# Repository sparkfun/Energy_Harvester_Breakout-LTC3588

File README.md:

SparkFun Energy Harvester Breakout - LTC3588
========================================

[*SparkFun Energy Harvester Breakout - LTC3588 (BOB-09946)*](https://www.sparkfun.com/products/9946)

This breakout board uses the LTC3588 Piezoelectric Energy Harvester from Linear Technologies. 
This board can be used not only for harvesting piezoelectric energy, but solar energy as well. 
There is a bridge rectified input for piezo elements (PZ1 and PZ2) and a direct input (VIN) for DC sources. 
Both are clamped to 20V. 
In addition, the board can simply be used as a standalone nanopower buck regulator.

Repository Contents
-------------------

* **/Hardware** - Eagle design files (.brd, .sch)
* **/Production** - Production panel files (.brd)

Documentation
--------------
* **[SparkFun Fritzing repo](https://github.com/sparkfun/Fritzing_Parts)** - Fritzing diagrams for SparkFun products.
* **[SparkFun 3D Model repo](https://github.com/sparkfun/3D_Models)** - 3D models of SparkFun products. 

License Information
-------------------
This product is _**open source**_! 

The **hardware** is released under [Creative Commons ShareAlike 4.0 International](https://creativecommons.org/licenses/by-sa/4.0/).

Please use, reuse, and modify these files as you see fit. Please maintain attribution to SparkFun Electronics and release anything derivative under the same license.

Distributed as-is; no warranty is given.

- Your friends at SparkFun.

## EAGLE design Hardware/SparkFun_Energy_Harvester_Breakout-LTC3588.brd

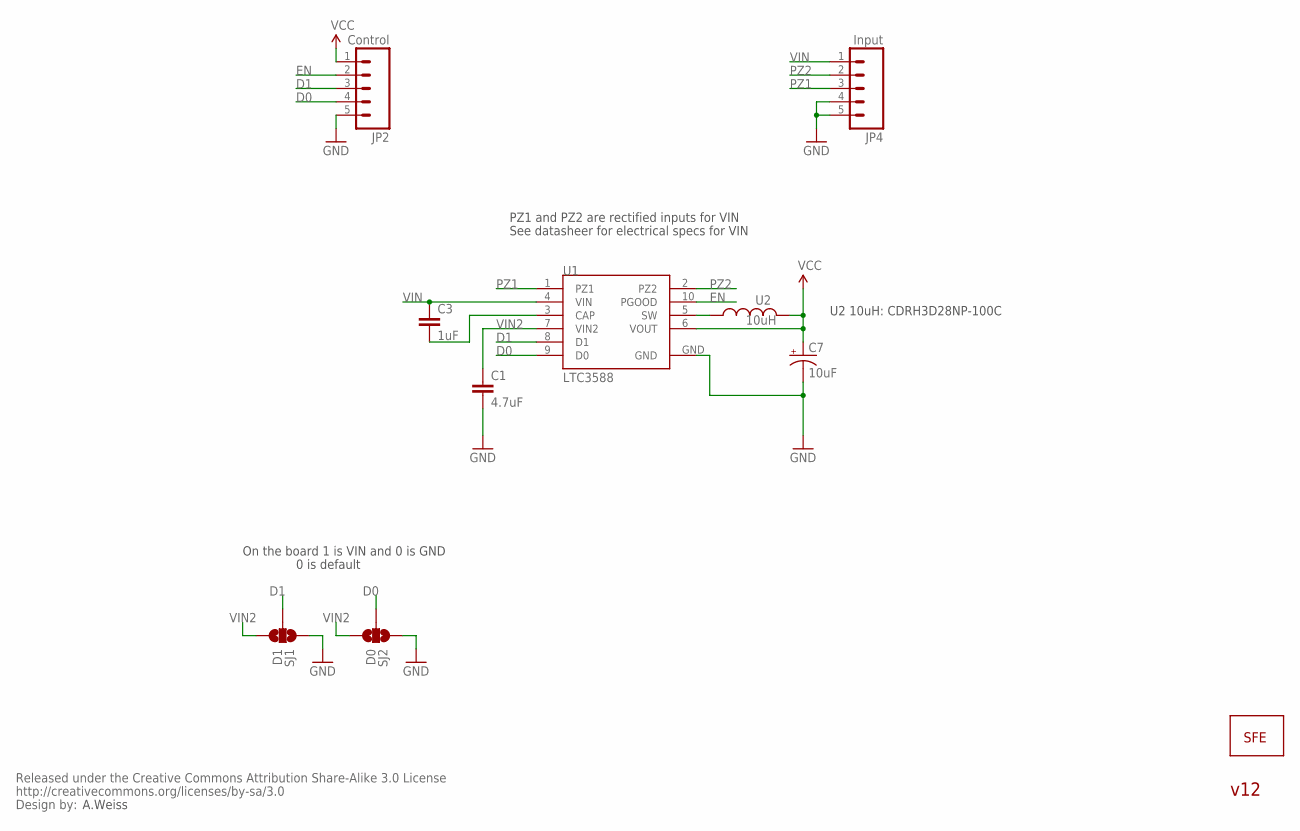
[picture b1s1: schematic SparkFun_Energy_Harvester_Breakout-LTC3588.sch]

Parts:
C1: 4.7uF; 0402-CAP
C3: 1uF; 0402-CAP
C7: 10uF; EIA3216
JP1: LOGO-SFESK; SFE-LOGO-FLAME
JP2: Control; 1X05
JP4: Input; 1X05
SJ1: D1; SJ_3_PASTE2&3
SJ2: D0; SJ_3_PASTE1&2
U1: LTC3588; MSOP-10-GNDPAD
U2: 10uH; CDRH3D28
U$1: CREATIVE_COMMONS

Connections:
D0: JP2.4, SJ2.2, U1.9 (D0)
D1: JP2.3, SJ1.2, U1.8 (D1)
EN: JP2.2, U1.10 (PGOOD)
GND: C1.2, C7.C (-), JP2.5, JP4.4, JP4.5, SJ1.1, SJ2.1, U1.GND
unnamed: C3.2, U1.3 (CAP)
unnamed: U1.5 (SW), U2.1
PZ1: JP4.3, U1.1 (PZ1)
PZ2: JP4.2, U1.2 (PZ2)
VCC: C7.A (+), JP2.1, U1.6 (VOUT), U2.2
VIN: C3.1, JP4.1, U1.4 (VIN)
VIN2: C1.1, SJ1.3, SJ2.3, U1.7 (VIN2)

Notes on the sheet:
U2 10uH: CDRH3D28NP-100C
A.Weiss
On the board 1 is VIN and 0 is GND
0 is default
PZ1 and PZ2 are rectified inputs for VIN
See datasheer for electrical specs for VIN
v12

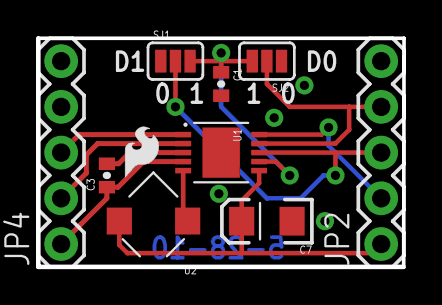
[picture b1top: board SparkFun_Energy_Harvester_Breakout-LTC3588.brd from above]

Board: 2 copper layers, 20.3 x 12.7 mm, 11 parts (0 on the bottom side), 11 nets.

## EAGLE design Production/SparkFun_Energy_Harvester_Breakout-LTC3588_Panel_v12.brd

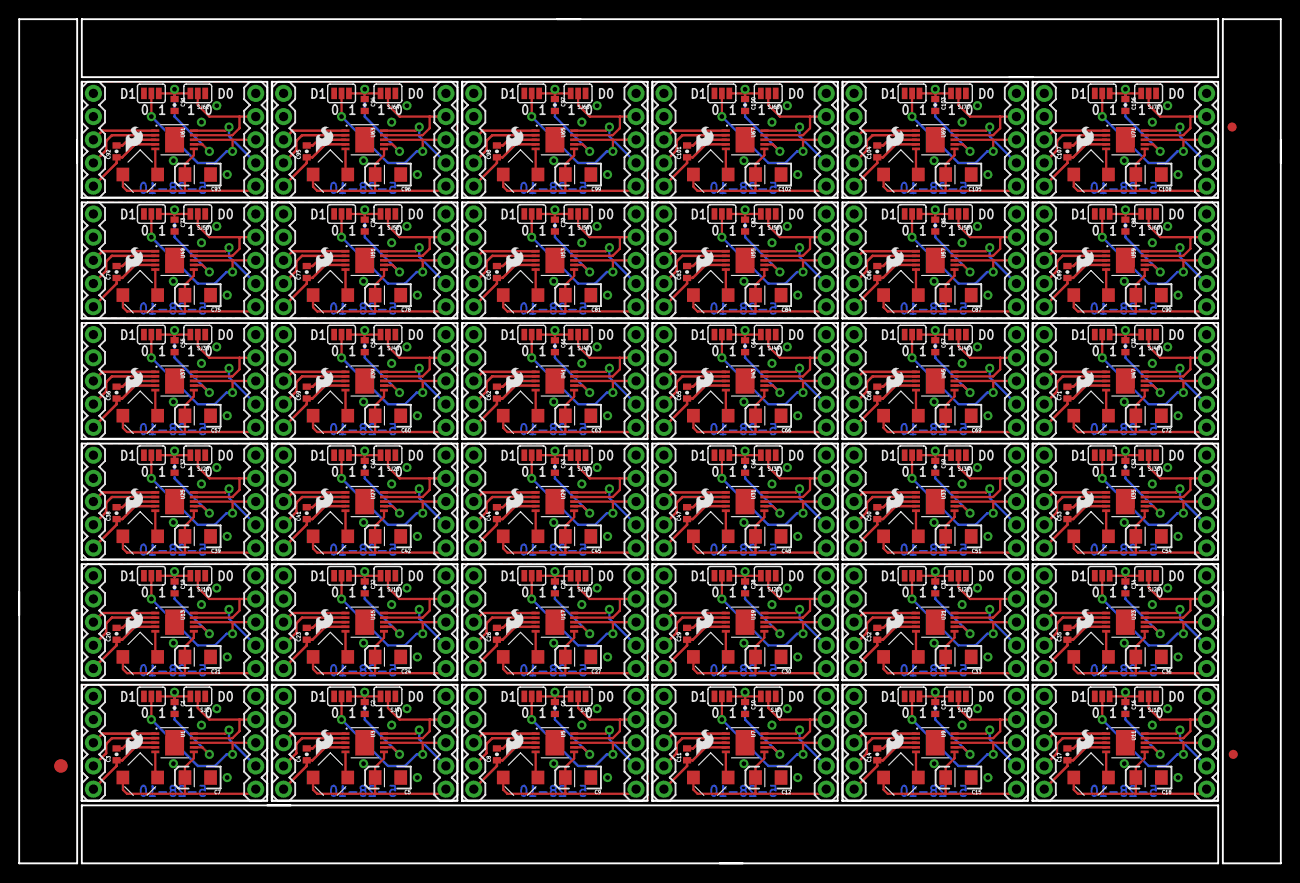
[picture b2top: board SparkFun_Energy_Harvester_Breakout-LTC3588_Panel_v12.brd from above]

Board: 2 copper layers, 138.1 x 92.4 mm, 363 parts (0 on the bottom side), 396 nets.

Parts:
C1, C2, C6, C10, C13, C16, C19, C22, C25, C28, C31, C34, C37, C40, C43, C46, C49, C52, C55, C58, C61, C64, C67, C70, C73, C76, C79, C82, C85, C88, C91, C94, C97, C100, C103, C106: 4.7uF; 0402-CAP
C3, C4, C8, C11, C14, C17, C20, C23, C26, C29, C32, C35, C38, C41, C44, C47, C50, C53, C56, C59, C62, C65, C68, C71, C74, C77, C80, C83, C86, C89, C92, C95, C98, C101, C104, C107: 1uF; 0402-CAP
C5, C7, C9, C12, C15, C18, C21, C24, C27, C30, C33, C36, C39, C42, C45, C48, C51, C54, C57, C60, C63, C66, C69, C72, C75, C78, C81, C84, C87, C90, C93, C96, C99, C102, C105, C108: 10uF; EIA3216
E$1: FIDUCIAL-1.5X3
E$5, E$7: FIDUCIAL-1X2
JP1, JP6, JP9, JP12, JP15, JP18, JP21, JP24, JP27, JP30, JP33, JP36, JP39, JP42, JP45, JP48, JP51, JP54, JP57, JP60, JP63, JP66, JP69, JP72, JP75, JP78, JP81, JP84, JP87, JP90, JP93, JP96, JP99, JP102, JP105, JP108: LOGO-SFESK; SFE-LOGO-FLAME
JP2, JP3, JP7, JP10, JP13, JP16, JP19, JP22, JP25, JP28, JP31, JP34, JP37, JP40, JP43, JP46, JP49, JP52, JP55, JP58, JP61, JP64, JP67, JP70, JP73, JP76, JP79, JP82, JP85, JP88, JP91, JP94, JP97, JP100, JP103, JP106: Control; 1X05
JP4, JP5, JP8, JP11, JP14, JP17, JP20, JP23, JP26, JP29, JP32, JP35, JP38, JP41, JP44, JP47, JP50, JP53, JP56, JP59, JP62, JP65, JP68, JP71, JP74, JP77, JP80, JP83, JP86, JP89, JP92, JP95, JP98, JP101, JP104, JP107: Input; 1X05
SJ1, SJ3, SJ5, SJ7, SJ9, SJ11, SJ13, SJ15, SJ17, SJ19, SJ21, SJ23, SJ25, SJ27, SJ29, SJ31, SJ33, SJ35, SJ37, SJ39, SJ41, SJ43, SJ45, SJ47, SJ49, SJ51, SJ53, SJ55, SJ57, SJ59, SJ61, SJ63, SJ65, SJ67, SJ69, SJ71: D1; SJ_3_PASTE2&3
SJ2, SJ4, SJ6, SJ8, SJ10, SJ12, SJ14, SJ16, SJ18, SJ20, SJ22, SJ24, SJ26, SJ28, SJ30, SJ32, SJ34, SJ36, SJ38, SJ40, SJ42, SJ44, SJ46, SJ48, SJ50, SJ52, SJ54, SJ56, SJ58, SJ60, SJ62, SJ64, SJ66, SJ68, SJ70, SJ72: D0; SJ_3_PASTE1&2
U1, U3, U5, U7, U9, U11, U13, U15, U17, U19, U21, U23, U25, U27, U29, U31, U33, U35, U37, U39, U41, U43, U45, U47, U49, U51, U53, U55, U57, U59, U61, U63, U65, U67, U69, U71: LTC3588; MSOP-10-GNDPAD
U2, U4, U6, U8, U10, U12, U14, U16, U18, U20, U22, U24, U26, U28, U30, U32, U34, U36, U38, U40, U42, U44, U46, U48, U50, U52, U54, U56, U58, U60, U62, U64, U66, U68, U70, U72: 10uH; CDRH3D28

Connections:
D0: JP2.4, SJ2.2, U1.9
D1: JP2.3, SJ1.2, U1.8
D2: JP3.3, SJ3.2, U3.8
D3: JP3.4, SJ4.2, U3.9
D4: JP7.3, SJ5.2, U5.8
D5: JP7.4, SJ6.2, U5.9
D6: JP10.3, SJ7.2, U7.8
D7: JP10.4, SJ8.2, U7.9
D8: JP13.3, SJ9.2, U9.8
D9: JP13.4, SJ10.2, U9.9
D10: JP16.3, SJ11.2, U11.8
D11: JP16.4, SJ12.2, U11.9
D12: JP19.3, SJ13.2, U13.8
D13: JP19.4, SJ14.2, U13.9
D14: JP22.3, SJ15.2, U15.8
D15: JP22.4, SJ16.2, U15.9
D16: JP25.3, SJ17.2, U17.8
D17: JP25.4, SJ18.2, U17.9
D18: JP28.3, SJ19.2, U19.8
D19: JP28.4, SJ20.2, U19.9
D20: JP31.3, SJ21.2, U21.8
D21: JP31.4, SJ22.2, U21.9
D22: JP34.3, SJ23.2, U23.8
D23: JP34.4, SJ24.2, U23.9
D24: JP37.3, SJ25.2, U25.8
D25: JP37.4, SJ26.2, U25.9
D26: JP40.3, SJ27.2, U27.8
D27: JP40.4, SJ28.2, U27.9
D28: JP43.3, SJ29.2, U29.8
D29: JP43.4, SJ30.2, U29.9
D30: JP46.3, SJ31.2, U31.8
D31: JP46.4, SJ32.2, U31.9
D32: JP49.3, SJ33.2, U33.8
D33: JP49.4, SJ34.2, U33.9
D34: JP52.3, SJ35.2, U35.8
D35: JP52.4, SJ36.2, U35.9
D36: JP55.3, SJ37.2, U37.8
D37: JP55.4, SJ38.2, U37.9
D38: JP58.3, SJ39.2, U39.8
D39: JP58.4, SJ40.2, U39.9
D40: JP61.3, SJ41.2, U41.8
D41: JP61.4, SJ42.2, U41.9
D42: JP64.3, SJ43.2, U43.8
D43: JP64.4, SJ44.2, U43.9
D44: JP67.3, SJ45.2, U45.8
D45: JP67.4, SJ46.2, U45.9
D46: JP70.3, SJ47.2, U47.8
D47: JP70.4, SJ48.2, U47.9
D48: JP73.3, SJ49.2, U49.8
D49: JP73.4, SJ50.2, U49.9
D50: JP76.3, SJ51.2, U51.8
D51: JP76.4, SJ52.2, U51.9
D52: JP79.3, SJ53.2, U53.8
D53: JP79.4, SJ54.2, U53.9
D54: JP82.3, SJ55.2, U55.8
D55: JP82.4, SJ56.2, U55.9
D56: JP85.3, SJ57.2, U57.8
D57: JP85.4, SJ58.2, U57.9
D58: JP88.3, SJ59.2, U59.8
D59: JP88.4, SJ60.2, U59.9
D60: JP91.3, SJ61.2, U61.8
D61: JP91.4, SJ62.2, U61.9
D62: JP94.3, SJ63.2, U63.8
D63: JP94.4, SJ64.2, U63.9
D64: JP97.3, SJ65.2, U65.8
D65: JP97.4, SJ66.2, U65.9
D66: JP100.3, SJ67.2, U67.8
D67: JP100.4, SJ68.2, U67.9
D68: JP103.3, SJ69.2, U69.8
D69: JP103.4, SJ70.2, U69.9
D70: JP106.3, SJ71.2, U71.8
D71: JP106.4, SJ72.2, U71.9
EN: JP2.2, U1.10
EN1: JP3.2, U3.10
EN2: JP7.2, U5.10
EN3: JP10.2, U7.10
EN4: JP13.2, U9.10
EN5: JP16.2, U11.10
EN6: JP19.2, U13.10
EN7: JP22.2, U15.10
EN8: JP25.2, U17.10
EN9: JP28.2, U19.10
EN10: JP31.2, U21.10
EN11: JP34.2, U23.10
EN12: JP37.2, U25.10
EN13: JP40.2, U27.10
EN14: JP43.2, U29.10
EN15: JP46.2, U31.10
EN16: JP49.2, U33.10
EN17: JP52.2, U35.10
EN18: JP55.2, U37.10
EN19: JP58.2, U39.10
EN20: JP61.2, U41.10
EN21: JP64.2, U43.10
EN22: JP67.2, U45.10
EN23: JP70.2, U47.10
EN24: JP73.2, U49.10
EN25: JP76.2, U51.10
EN26: JP79.2, U53.10
EN27: JP82.2, U55.10
EN28: JP85.2, U57.10
EN29: JP88.2, U59.10
EN30: JP91.2, U61.10
EN31: JP94.2, U63.10
EN32: JP97.2, U65.10
EN33: JP100.2, U67.10
EN34: JP103.2, U69.10
EN35: JP106.2, U71.10
GND: C1.2, C7.C, JP2.5, JP4.4, JP4.5, SJ1.1, SJ2.1, U1.GND
GND1: C2.2, C5.C, JP3.5, JP5.4, JP5.5, SJ3.1, SJ4.1, U3.GND
GND2: C6.2, C9.C, JP7.5, JP8.4, JP8.5, SJ5.1, SJ6.1, U5.GND
GND3: C10.2, C12.C, JP10.5, JP11.4, JP11.5, SJ7.1, SJ8.1, U7.GND
GND4: C13.2, C15.C, JP13.5, JP14.4, JP14.5, SJ9.1, SJ10.1, U9.GND
GND5: C16.2, C18.C, JP16.5, JP17.4, JP17.5, SJ11.1, SJ12.1, U11.GND
GND6: C19.2, C21.C, JP19.5, JP20.4, JP20.5, SJ13.1, SJ14.1, U13.GND
GND7: C22.2, C24.C, JP22.5, JP23.4, JP23.5, SJ15.1, SJ16.1, U15.GND
GND8: C25.2, C27.C, JP25.5, JP26.4, JP26.5, SJ17.1, SJ18.1, U17.GND
GND9: C28.2, C30.C, JP28.5, JP29.4, JP29.5, SJ19.1, SJ20.1, U19.GND
GND10: C31.2, C33.C, JP31.5, JP32.4, JP32.5, SJ21.1, SJ22.1, U21.GND
GND11: C34.2, C36.C, JP34.5, JP35.4, JP35.5, SJ23.1, SJ24.1, U23.GND
GND12: C37.2, C39.C, JP37.5, JP38.4, JP38.5, SJ25.1, SJ26.1, U25.GND
GND13: C40.2, C42.C, JP40.5, JP41.4, JP41.5, SJ27.1, SJ28.1, U27.GND
GND14: C43.2, C45.C, JP43.5, JP44.4, JP44.5, SJ29.1, SJ30.1, U29.GND
GND15: C46.2, C48.C, JP46.5, JP47.4, JP47.5, SJ31.1, SJ32.1, U31.GND
GND16: C49.2, C51.C, JP49.5, JP50.4, JP50.5, SJ33.1, SJ34.1, U33.GND
GND17: C52.2, C54.C, JP52.5, JP53.4, JP53.5, SJ35.1, SJ36.1, U35.GND
GND18: C55.2, C57.C, JP55.5, JP56.4, JP56.5, SJ37.1, SJ38.1, U37.GND
GND19: C58.2, C60.C, JP58.5, JP59.4, JP59.5, SJ39.1, SJ40.1, U39.GND
GND20: C61.2, C63.C, JP61.5, JP62.4, JP62.5, SJ41.1, SJ42.1, U41.GND
GND21: C64.2, C66.C, JP64.5, JP65.4, JP65.5, SJ43.1, SJ44.1, U43.GND
GND22: C67.2, C69.C, JP67.5, JP68.4, JP68.5, SJ45.1, SJ46.1, U45.GND
GND23: C70.2, C72.C, JP70.5, JP71.4, JP71.5, SJ47.1, SJ48.1, U47.GND
GND24: C73.2, C75.C, JP73.5, JP74.4, JP74.5, SJ49.1, SJ50.1, U49.GND
GND25: C76.2, C78.C, JP76.5, JP77.4, JP77.5, SJ51.1, SJ52.1, U51.GND
GND26: C79.2, C81.C, JP79.5, JP80.4, JP80.5, SJ53.1, SJ54.1, U53.GND
GND27: C82.2, C84.C, JP82.5, JP83.4, JP83.5, SJ55.1, SJ56.1, U55.GND
GND28: C85.2, C87.C, JP85.5, JP86.4, JP86.5, SJ57.1, SJ58.1, U57.GND
GND29: C88.2, C90.C, JP88.5, JP89.4, JP89.5, SJ59.1, SJ60.1, U59.GND
GND30: C91.2, C93.C, JP91.5, JP92.4, JP92.5, SJ61.1, SJ62.1, U61.GND
GND31: C94.2, C96.C, JP94.5, JP95.4, JP95.5, SJ63.1, SJ64.1, U63.GND
GND32: C97.2, C99.C, JP97.5, JP98.4, JP98.5, SJ65.1, SJ66.1, U65.GND
GND33: C100.2, C102.C, JP100.5, JP101.4, JP101.5, SJ67.1, SJ68.1, U67.GND
GND34: C103.2, C105.C, JP103.5, JP104.4, JP104.5, SJ69.1, SJ70.1, U69.GND
GND35: C106.2, C108.C, JP106.5, JP107.4, JP107.5, SJ71.1, SJ72.1, U71.GND
unnamed: C4.2, U3.3
unnamed: C3.2, U1.3
unnamed: U3.5, U4.1
unnamed: C8.2, U5.3
unnamed: U5.5, U6.1
unnamed: U1.5, U2.1
unnamed: C11.2, U7.3
unnamed: U7.5, U8.1
unnamed: C14.2, U9.3
unnamed: U9.5, U10.1
unnamed: C17.2, U11.3
unnamed: U11.5, U12.1
unnamed: C20.2, U13.3
unnamed: U13.5, U14.1
unnamed: C23.2, U15.3
unnamed: U15.5, U16.1
unnamed: C26.2, U17.3
unnamed: U17.5, U18.1
unnamed: C29.2, U19.3
unnamed: U19.5, U20.1
unnamed: C32.2, U21.3
unnamed: U21.5, U22.1
unnamed: C35.2, U23.3
unnamed: U23.5, U24.1
unnamed: C38.2, U25.3
unnamed: U25.5, U26.1
unnamed: C41.2, U27.3
unnamed: U27.5, U28.1
unnamed: C44.2, U29.3
unnamed: U29.5, U30.1
unnamed: C47.2, U31.3
unnamed: U31.5, U32.1
unnamed: C50.2, U33.3
unnamed: U33.5, U34.1
unnamed: C53.2, U35.3
unnamed: U35.5, U36.1
unnamed: C56.2, U37.3
unnamed: U37.5, U38.1
unnamed: C59.2, U39.3
unnamed: U39.5, U40.1
unnamed: C62.2, U41.3
unnamed: U41.5, U42.1
unnamed: C65.2, U43.3
unnamed: U43.5, U44.1
unnamed: C68.2, U45.3
unnamed: U45.5, U46.1
unnamed: C71.2, U47.3
unnamed: U47.5, U48.1
unnamed: C74.2, U49.3
unnamed: U49.5, U50.1
unnamed: C77.2, U51.3
unnamed: U51.5, U52.1
unnamed: C80.2, U53.3
unnamed: U53.5, U54.1
unnamed: C83.2, U55.3
unnamed: U55.5, U56.1
unnamed: C86.2, U57.3
unnamed: U57.5, U58.1
unnamed: C89.2, U59.3
unnamed: U59.5, U60.1
unnamed: C92.2, U61.3
unnamed: U61.5, U62.1
unnamed: C95.2, U63.3
unnamed: U63.5, U64.1
unnamed: C98.2, U65.3
unnamed: U65.5, U66.1
unnamed: C101.2, U67.3
unnamed: U67.5, U68.1
unnamed: C104.2, U69.3
unnamed: U69.5, U70.1
unnamed: C107.2, U71.3
unnamed: U71.5, U72.1
PZ1: JP4.3, U1.1
PZ2: JP4.2, U1.2
PZ3: JP5.2, U3.2
PZ4: JP5.3, U3.1
PZ5: JP8.2, U5.2
PZ6: JP8.3, U5.1
PZ7: JP11.2, U7.2
PZ8: JP11.3, U7.1
PZ9: JP14.2, U9.2
PZ10: JP14.3, U9.1
PZ11: JP17.2, U11.2
PZ12: JP17.3, U11.1
PZ13: JP20.2, U13.2
PZ14: JP20.3, U13.1
PZ15: JP23.2, U15.2
PZ16: JP23.3, U15.1
PZ17: JP26.2, U17.2
PZ18: JP26.3, U17.1
PZ19: JP29.2, U19.2
PZ20: JP29.3, U19.1
PZ21: JP32.2, U21.2
PZ22: JP32.3, U21.1
PZ23: JP35.2, U23.2
PZ24: JP35.3, U23.1
PZ25: JP38.2, U25.2
PZ26: JP38.3, U25.1
PZ27: JP41.2, U27.2
PZ28: JP41.3, U27.1
PZ29: JP44.2, U29.2
PZ30: JP44.3, U29.1
PZ31: JP47.2, U31.2
PZ32: JP47.3, U31.1
PZ33: JP50.2, U33.2
PZ34: JP50.3, U33.1
PZ35: JP53.2, U35.2
PZ36: JP53.3, U35.1
PZ37: JP56.2, U37.2
PZ38: JP56.3, U37.1
PZ39: JP59.2, U39.2
PZ40: JP59.3, U39.1
PZ41: JP62.2, U41.2
PZ42: JP62.3, U41.1
PZ43: JP65.2, U43.2
PZ44: JP65.3, U43.1
PZ45: JP68.2, U45.2
PZ46: JP68.3, U45.1
PZ47: JP71.2, U47.2
PZ48: JP71.3, U47.1
PZ49: JP74.2, U49.2
PZ50: JP74.3, U49.1
PZ51: JP77.2, U51.2
PZ52: JP77.3, U51.1
PZ53: JP80.2, U53.2
PZ54: JP80.3, U53.1
PZ55: JP83.2, U55.2
PZ56: JP83.3, U55.1
PZ57: JP86.2, U57.2
PZ58: JP86.3, U57.1
PZ59: JP89.2, U59.2
PZ60: JP89.3, U59.1
PZ61: JP92.2, U61.2
PZ62: JP92.3, U61.1
PZ63: JP95.2, U63.2
PZ64: JP95.3, U63.1
PZ65: JP98.2, U65.2
PZ66: JP98.3, U65.1
PZ67: JP101.2, U67.2
PZ68: JP101.3, U67.1
PZ69: JP104.2, U69.2
PZ70: JP104.3, U69.1
PZ71: JP107.2, U71.2
PZ72: JP107.3, U71.1
VCC: C7.A, JP2.1, U1.6, U2.2
VCC1: C5.A, JP3.1, U3.6, U4.2
VCC2: C9.A, JP7.1, U5.6, U6.2
VCC3: C12.A, JP10.1, U7.6, U8.2
VCC4: C15.A, JP13.1, U9.6, U10.2
VCC5: C18.A, JP16.1, U11.6, U12.2
VCC6: C21.A, JP19.1, U13.6, U14.2
VCC7: C24.A, JP22.1, U15.6, U16.2
VCC8: C27.A, JP25.1, U17.6, U18.2
VCC9: C30.A, JP28.1, U19.6, U20.2
VCC10: C33.A, JP31.1, U21.6, U22.2
VCC11: C36.A, JP34.1, U23.6, U24.2
VCC12: C39.A, JP37.1, U25.6, U26.2
VCC13: C42.A, JP40.1, U27.6, U28.2
VCC14: C45.A, JP43.1, U29.6, U30.2
VCC15: C48.A, JP46.1, U31.6, U32.2
VCC16: C51.A, JP49.1, U33.6, U34.2
VCC17: C54.A, JP52.1, U35.6, U36.2
VCC18: C57.A, JP55.1, U37.6, U38.2
VCC19: C60.A, JP58.1, U39.6, U40.2
VCC20: C63.A, JP61.1, U41.6, U42.2
VCC21: C66.A, JP64.1, U43.6, U44.2
VCC22: C69.A, JP67.1, U45.6, U46.2
VCC23: C72.A, JP70.1, U47.6, U48.2
VCC24: C75.A, JP73.1, U49.6, U50.2
VCC25: C78.A, JP76.1, U51.6, U52.2
VCC26: C81.A, JP79.1, U53.6, U54.2
VCC27: C84.A, JP82.1, U55.6, U56.2
VCC28: C87.A, JP85.1, U57.6, U58.2
VCC29: C90.A, JP88.1, U59.6, U60.2
VCC30: C93.A, JP91.1, U61.6, U62.2
VCC31: C96.A, JP94.1, U63.6, U64.2
VCC32: C99.A, JP97.1, U65.6, U66.2
VCC33: C102.A, JP100.1, U67.6, U68.2
VCC34: C105.A, JP103.1, U69.6, U70.2
VCC35: C108.A, JP106.1, U71.6, U72.2
VIN: C3.1, JP4.1, U1.4
VIN1: C2.1, SJ3.3, SJ4.3, U3.7
VIN2: C1.1, SJ1.3, SJ2.3, U1.7
VIN3: C4.1, JP5.1, U3.4
VIN4: C6.1, SJ5.3, SJ6.3, U5.7
VIN5: C8.1, JP8.1, U5.4
VIN6: C10.1, SJ7.3, SJ8.3, U7.7
VIN7: C11.1, JP11.1, U7.4
VIN8: C13.1, SJ9.3, SJ10.3, U9.7
VIN9: C14.1, JP14.1, U9.4
VIN10: C16.1, SJ11.3, SJ12.3, U11.7
VIN11: C17.1, JP17.1, U11.4
VIN12: C19.1, SJ13.3, SJ14.3, U13.7
VIN13: C20.1, JP20.1, U13.4
VIN14: C22.1, SJ15.3, SJ16.3, U15.7
VIN15: C23.1, JP23.1, U15.4
VIN16: C25.1, SJ17.3, SJ18.3, U17.7
VIN17: C26.1, JP26.1, U17.4
VIN18: C28.1, SJ19.3, SJ20.3, U19.7
VIN19: C29.1, JP29.1, U19.4
VIN20: C31.1, SJ21.3, SJ22.3, U21.7
VIN21: C32.1, JP32.1, U21.4
VIN22: C34.1, SJ23.3, SJ24.3, U23.7
VIN23: C35.1, JP35.1, U23.4
VIN24: C37.1, SJ25.3, SJ26.3, U25.7
VIN25: C38.1, JP38.1, U25.4
VIN26: C40.1, SJ27.3, SJ28.3, U27.7
VIN27: C41.1, JP41.1, U27.4
VIN28: C43.1, SJ29.3, SJ30.3, U29.7
VIN29: C44.1, JP44.1, U29.4
VIN30: C46.1, SJ31.3, SJ32.3, U31.7
VIN31: C47.1, JP47.1, U31.4
VIN32: C49.1, SJ33.3, SJ34.3, U33.7
VIN33: C50.1, JP50.1, U33.4
VIN34: C52.1, SJ35.3, SJ36.3, U35.7
VIN35: C53.1, JP53.1, U35.4
VIN36: C55.1, SJ37.3, SJ38.3, U37.7
VIN37: C56.1, JP56.1, U37.4
VIN38: C58.1, SJ39.3, SJ40.3, U39.7
VIN39: C59.1, JP59.1, U39.4
VIN40: C61.1, SJ41.3, SJ42.3, U41.7
VIN41: C62.1, JP62.1, U41.4
VIN42: C64.1, SJ43.3, SJ44.3, U43.7
VIN43: C65.1, JP65.1, U43.4
VIN44: C67.1, SJ45.3, SJ46.3, U45.7
VIN45: C68.1, JP68.1, U45.4
VIN46: C70.1, SJ47.3, SJ48.3, U47.7
VIN47: C71.1, JP71.1, U47.4
VIN48: C73.1, SJ49.3, SJ50.3, U49.7
VIN49: C74.1, JP74.1, U49.4
VIN50: C76.1, SJ51.3, SJ52.3, U51.7
VIN51: C77.1, JP77.1, U51.4
VIN52: C79.1, SJ53.3, SJ54.3, U53.7
VIN53: C80.1, JP80.1, U53.4
VIN54: C82.1, SJ55.3, SJ56.3, U55.7
VIN55: C83.1, JP83.1, U55.4
VIN56: C85.1, SJ57.3, SJ58.3, U57.7
VIN57: C86.1, JP86.1, U57.4
VIN58: C88.1, SJ59.3, SJ60.3, U59.7
VIN59: C89.1, JP89.1, U59.4
VIN60: C91.1, SJ61.3, SJ62.3, U61.7
VIN61: C92.1, JP92.1, U61.4
VIN62: C94.1, SJ63.3, SJ64.3, U63.7
VIN63: C95.1, JP95.1, U63.4
VIN64: C97.1, SJ65.3, SJ66.3, U65.7
VIN65: C98.1, JP98.1, U65.4
VIN66: C100.1, SJ67.3, SJ68.3, U67.7
VIN67: C101.1, JP101.1, U67.4
VIN68: C103.1, SJ69.3, SJ70.3, U69.7
VIN69: C104.1, JP104.1, U69.4
VIN70: C106.1, SJ71.3, SJ72.3, U71.7
VIN71: C107.1, JP107.1, U71.4

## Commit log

2015-05-06 Adding hardware, readme
2015-10-19 created new v12 panel

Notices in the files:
parts and their libraries:
SparkFun: Released under the Creative Commons Attribution Share-Alike 3.0 License
SparkFun: http://creativecommons.org/licenses/by-sa/3.0
SparkFun-Aesthetics: Licensing: CC v3.0 Share-Alike You are welcome to use this library for commercial purposes.
